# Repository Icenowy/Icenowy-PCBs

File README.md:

# Icenowy-PCBs
PCBs designed by Icenowy

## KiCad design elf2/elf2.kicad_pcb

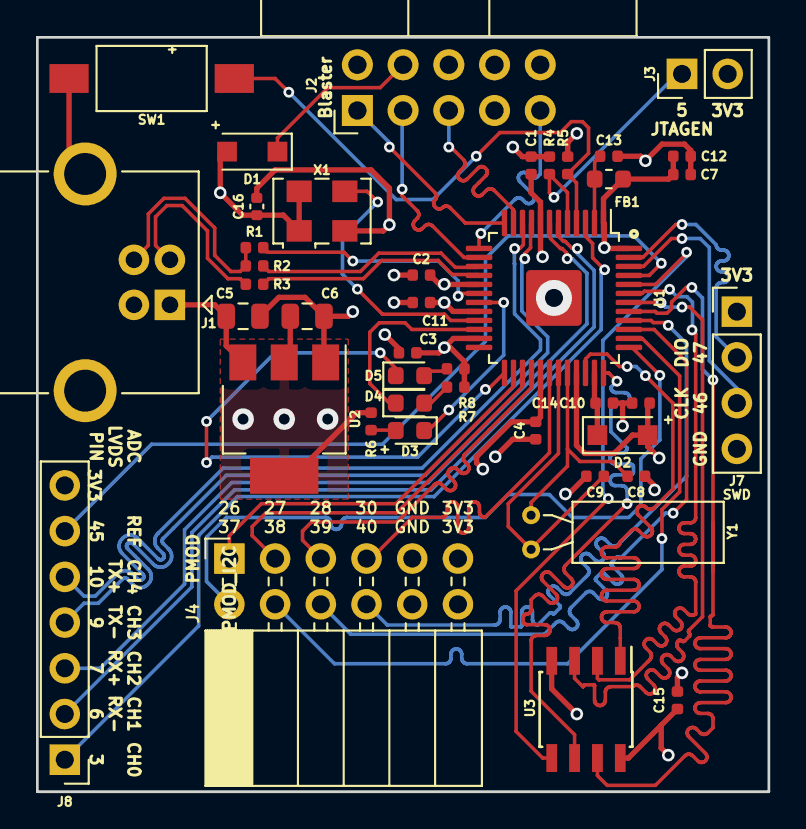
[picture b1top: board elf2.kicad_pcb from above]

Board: 4 copper layers, 40.6 x 41.9 mm, 42 parts (0 on the bottom side), 48 nets.

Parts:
C1, C2, C3, C4, C7, C10, C11, C12, C13, C14, C15, C16: 0.1uF; C_0402_1005Metric
C5, C6: 10uF; C_0805_2012Metric
C8, C9: 12pF; C_0402_1005Metric
D1, D2: 1N5819; D_SOD-123F
D3: RED; LED_0603_1608Metric
D4: GREEN; LED_0603_1608Metric
D5: BLUE; LED_0603_1608Metric
FB1: 300R; L_0603_1608Metric
J1: USB_B; USB_B_OST_USB-B1HSxx_Horizontal
J2: USB_Blaster; IDC-Header_2x05_P2.54mm_Horizontal
J3: JTAGEN; PinHeader_1x02_P2.54mm_Vertical
J4: PMOD; PinSocket_2x06_P2.54mm_Horizontal
J7: SWD; PinHeader_1x04_P2.54mm_Vertical
J8: ADC_LVDS; PinHeader_1x07_P2.54mm_Vertical
R1, R6, R7, R8: 1.5kR; R_0402_1005Metric
R2, R3: 47R; R_0402_1005Metric
R4, R5: 10kR; R_0402_1005Metric
SW1: RESET; SW_SPST_FSMSM
U1: EF2M45LG48; LQFP-48-1EP_7x7mm_P0.5mm_EP3.1x3.1mm
U2: AP1117-33; SOT-223-3_TabPin2
U3: AT25SF081-SSHD-X; SOIC-8_3.9x4.9mm_P1.27mm
X1: 24MHz; Oscillator_SMD_EuroQuartz_XO53-4Pin_5.0x3.2mm
Y1: 32768; Crystal_C38-LF_D3.0mm_L8.0mm_Horizontal

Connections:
+3V3: C1.2, C2.2, C3.2, C4.2, C6.1, C7.2, C10.1, C11.1, C12.1, C15.2, C16.1, D1.2, D2.2, FB1.1, J3.2, J4.11, J4.12, J7.1, J8.7, R5.1, R6.1, R7.1, R8.1, U1.1, U1.8, U1.17, U1.20, U1.23, U1.29, U1.33, U1.48, U2.2, U3.8, X1.1, X1.4
+5V: C5.1, J1.1, U2.3
+BATT: C14.2, D2.1, U1.35
/ADC_0: J8.1, U1.3
/ADC_REF: J8.6, U1.45
/CLK: U1.21, X1.3
/JTAGEN: J3.1, R4.1, U1.5
/LED_B: D5.1, U1.25
/LED_G: D4.1, U1.22
/LED_R: D3.1, U1.19
/LVDSRX_N: J8.2, U1.6
/LVDSRX_P: J8.3, U1.7
/LVDSTX_N: J8.4, U1.9
/LVDSTX_P: J8.5, U1.10
/PMOD_6P2_1: J4.2, U1.37
/PMOD_6P2_2: J4.4, U1.38
/PMOD_6P2_3: J4.6, U1.39
/PMOD_6P2_4: J4.8, U1.40
/PMOD_6P_1: J4.1, U1.26
/PMOD_6P_2: J4.3, U1.27
/PMOD_6P_3: J4.5, U1.28
/PMOD_6P_4: J4.7, U1.30
/PORT_D+: J1.3, R1.2, R2.2
/PORT_D-: J1.2, R3.2
/PROGRAMN: R5.2, SW1.1, U1.4
/QSPI_CS: U1.34, U3.1
/QSPI_IO0: U1.44, U3.5
/QSPI_IO1: U1.43, U3.2
/QSPI_IO2: U1.42, U3.3
/QSPI_IO3: U1.41, U3.7
/QSPI_SCK: U1.36, U3.6
/SWCLK: J7.3, U1.46
/SWDIO: J7.2, U1.47
/TCK: J2.1, U1.12
/TDI: J2.9, U1.13
/TDO: J2.3, U1.14
/TMS: J2.5, U1.11
/UD+: R2.1, U1.15
/UD-: R3.1, U1.16
/UPU: R1.1, U1.18
GND: C1.1, C2.1, C3.1, C4.1, C5.2, C6.2, C7.1, C8.2, C9.2, C10.2, C11.2, C12.2, C13.1, C14.1, C15.1, C16.2, J1.4, J1.5, J2.2, J2.10, J4.9, J4.10, J7.4, R4.2, SW1.2, U1.49, U2.1, U3.4, X1.2
unnamed: C8.1, U1.32, Y1.2
unnamed: C9.1, U1.31, Y1.1
unnamed: C13.2, FB1.2, U1.2
unnamed: D1.1, J2.4
unnamed: D3.2, R6.2
unnamed: D4.2, R7.2
unnamed: D5.2, R8.2

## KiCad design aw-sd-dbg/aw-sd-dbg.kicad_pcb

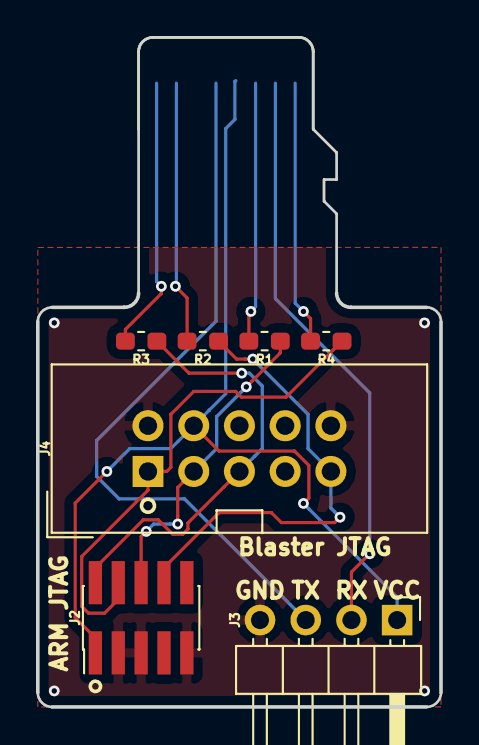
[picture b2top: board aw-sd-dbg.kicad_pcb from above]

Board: 2 copper layers, 22.4 x 37.2 mm, 8 parts (0 on the bottom side), 12 nets.

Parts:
J1: MicroSD
J2: ARM JTAG; PinHeader_2x05_P1.27mm_Vertical_SMD
J3: Conn_01x04_Male; PinHeader_1x04_P2.54mm_Horizontal
J4: Blaster JTAG; IDC-Header_2x05_P2.54mm_Vertical
R1, R2, R3, R4: 47R; R_0603_1608Metric_Pad1.05x0.95mm_HandSolder

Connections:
/CLK: J1.5, J3.3
/CMD: J1.3, R1.2
/DAT0: J1.7, R2.2
/DAT1: J1.8, R3.2
/DAT2: J1.1, R4.2
/DAT3: J1.2, J3.2
/JTCK_O: J2.4, J4.1, R4.1
/JTDI_O: J2.8, J4.9, R2.1
/JTDO_O: J2.6, J4.3, R1.1
/JTMS_O: J2.2, J4.5, R3.1
/VTGT: J1.4, J2.1, J3.1, J4.4
GND: J1.6, J2.3, J2.5, J2.9, J3.4, J4.2, J4.10

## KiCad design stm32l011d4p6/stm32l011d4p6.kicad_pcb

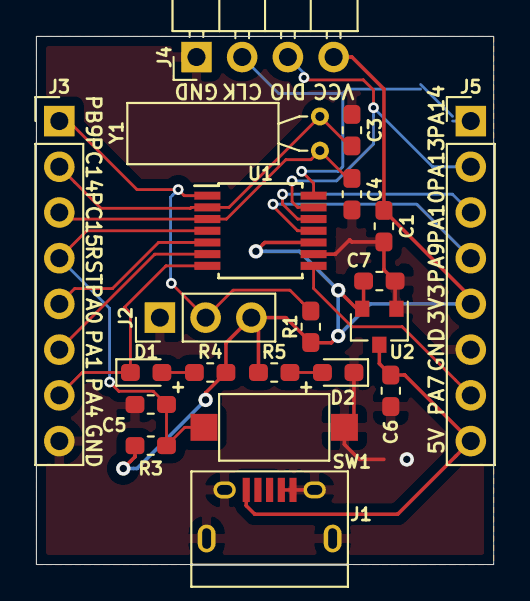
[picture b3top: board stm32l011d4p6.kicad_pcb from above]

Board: 2 copper layers, 25.4 x 29.3 mm, 21 parts (0 on the bottom side), 17 nets.

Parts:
C1, C5, C6, C7: 0.1uF; C_0603_1608Metric_Pad1.05x0.95mm_HandSolder
C3, C4: 12pF; C_0603_1608Metric_Pad1.05x0.95mm_HandSolder
D1: GREEN; LED_0603_1608Metric_Pad1.05x0.95mm_HandSolder
D2: RED; LED_0603_1608Metric_Pad1.05x0.95mm_HandSolder
J1: USB_B_Micro; USB_Micro-B_Connector
J2: BOOT0; PinHeader_1x03_P2.54mm_Vertical
J3: LEFT; PinHeader_1x08_P2.54mm_Vertical
J4: SWD; PinHeader_1x04_P2.54mm_Horizontal
J5: RIGHT; PinHeader_1x08_P2.54mm_Vertical
R1, R3: 10kR; R_0603_1608Metric_Pad1.05x0.95mm_HandSolder
R4, R5: 1.5kR; R_0603_1608Metric_Pad1.05x0.95mm_HandSolder
SW1: SW_Push; SW_SPST_CK_RS282G05A3
U1: STM32L011D4Px; TSSOP-14_4.4x5mm_P0.65mm
U2: SC662K-3.3V; SOT-23
Y1: 32768Hz; Crystal_C38-LF_D3.0mm_L8.0mm_Horizontal

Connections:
/BOOT0: J2.2, J3.1, R1.1, U1.1
/NRST: C5.1, J3.4, R3.2, SW1.1, U1.4
/OSC_IN: C3.2, J3.2, U1.2, Y1.1
/OSC_OUT: C4.2, J3.3, U1.3, Y1.2
/PA0: J3.5, U1.5
/PA1: J3.6, U1.6
/PA4: D1.1, J3.7, U1.7
/PA7: J5.7, U1.8
/PA9: J5.4, U1.11
/PA10: J5.3, U1.12
/PA13: J4.3, J5.2, U1.13
/PA14: J4.2, J5.1, U1.14
GND: C1.1, C3.1, C4.1, C5.2, C6.1, C7.2, D2.1, J1.4, J1.5, J1.6, J2.1, J3.8, J4.1, J5.6, SW1.2, U1.9, U2.1
unnamed: D1.2, R4.2
unnamed: D2.2, R5.2
VBUS: C6.2, J1.1, J5.8, U2.3
VCC: C1.2, C7.1, J2.3, J4.4, J5.5, R1.2, R3.1, R4.1, R5.1, U1.10, U2.2

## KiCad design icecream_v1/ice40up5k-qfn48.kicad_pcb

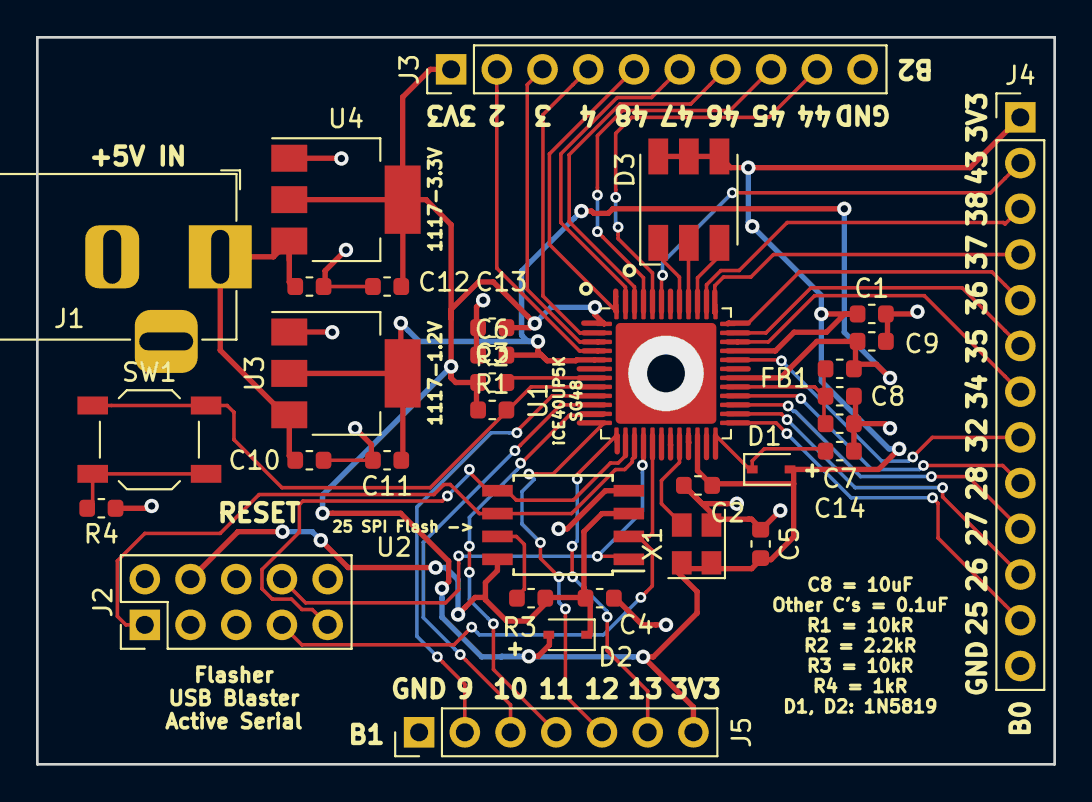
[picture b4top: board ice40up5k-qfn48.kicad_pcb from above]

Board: 2 copper layers, 56.5 x 40.4 mm, 33 parts (0 on the bottom side), 43 nets.

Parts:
C1, C2, C3, C4, C5, C6, C7, C9, C10, C11, C12, C13, C14: 0.1uF; C_0603_1608Metric
C8: 10uF; C_0603_1608Metric
D1, D2: 1N5819; D_SOD-323
D3: LED_RGB; LED_RGB_5050-6
FB1: Ferrite_Bead; L_0603_1608Metric
J1: 5V 3.5mm/1.35mm; BarrelJack_Horizontal
J2: Flasher; PinHeader_2x05_P2.54mm_Vertical
J3: Bank 2; PinHeader_1x10_P2.54mm_Vertical
J4: Bank 0; PinHeader_1x13_P2.54mm_Vertical
J5: Bank 1; PinHeader_1x07_P2.54mm_Vertical
R1, R3: 10kR; R_0603_1608Metric
R2: 2.2kR; R_0603_1608Metric
R4: 1kR; R_0603_1608Metric
SW1: Button; SW_SPST_TL3342
U1: ICE40UP5K-SG48ITR; QFN-48-1EP_7x7mm_P0.5mm_EP5.6x5.6mm
U2: W25Q80; SOIJ-8_5.3x5.3mm_P1.27mm
U3: LD1117S12TR_SOT223; SOT-223-3_TabPin2
U4: LD1117S33TR_SOT223; SOT-223-3_TabPin2
X1: 50MHz; Oscillator_SMD_Abracon_ASE-4Pin_3.2x2.5mm

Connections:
+1V2: C6.2, C9.2, C11.1, FB1.1, U1.5, U1.30, U3.2
+3.3VP: C4.1, D2.1, J2.4, R3.1, U2.3, U2.8
+3V3: C1.1, C2.1, C3.1, C5.1, C13.1, D1.2, D2.2, D3.4, D3.5, D3.6, J3.1, J4.1, J5.7, R1.1, R2.1, U1.1, U1.22, U1.33, U4.2, X1.1, X1.4
+5V: C10.1, C12.1, J1.1, U3.3, U4.3
/2: J3.4, U1.2
/3: J3.3, U1.3
/4: J3.2, U1.4
/9: J5.2, U1.9
/10: J5.3, U1.10
/11: J5.4, U1.11
/12: J5.5, U1.12
/13: J5.6, U1.13
/25: J4.12, U1.25
/26: J4.11, U1.26
/27: J4.10, U1.27
/28: J4.9, U1.28
/32: J4.8, U1.32
/34: J4.7, U1.34
/35: J4.6, U1.35
/36: J4.5, U1.36
/37: J4.4, U1.37
/38: J4.3, U1.38
/43: J4.2, U1.43
/44: J3.9, U1.44
/45: J3.8, U1.45
/46: J3.7, U1.46
/47: J3.6, U1.47
/48: J3.5, U1.48
/CDONE: R2.2, U1.7
/CLK_50M: U1.20, X1.3
/CRESET: R1.2, SW1.1, U1.8
/ICE_SCK: J2.1, U1.15, U2.6
/ICE_SI: J2.7, U1.17, U2.2
/ICE_SO: J2.9, U1.14, U2.5
/ICE_SS: J2.8, U1.16, U2.1
GND: C1.2, C2.2, C3.2, C4.2, C5.2, C6.1, C7.1, C8.1, C9.1, C10.2, C11.2, C12.2, C13.2, C14.2, J1.2, J2.2, J2.10, J3.10, J4.13, J5.1, R4.1, U1.49, U2.4, U3.1, U4.1, X1.2
unnamed: C7.2, C8.2, FB1.2, U1.29
unnamed: C14.1, D1.1, U1.24
unnamed: D3.1, U1.41
unnamed: D3.2, U1.40
unnamed: D3.3, U1.39
unnamed: R3.2, U2.7
unnamed: R4.2, SW1.2

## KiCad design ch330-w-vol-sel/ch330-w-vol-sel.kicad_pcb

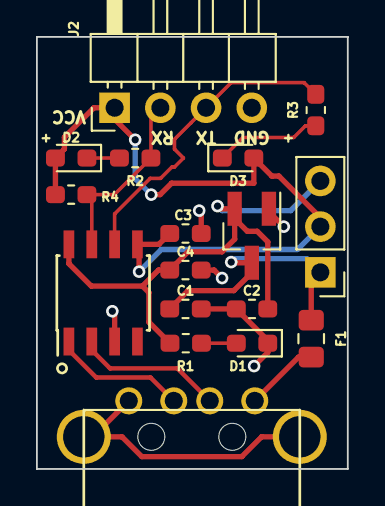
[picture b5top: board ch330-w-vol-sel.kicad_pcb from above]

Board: 2 copper layers, 17.3 x 24.0 mm, 17 parts (0 on the bottom side), 12 nets.

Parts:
C1, C2: 1uF; C_0603_1608Metric_Pad1.05x0.95mm_HandSolder
C3, C4: 0.1uF; C_0603_1608Metric_Pad1.05x0.95mm_HandSolder
D1: RED; LED_0603_1608Metric_Pad1.05x0.95mm_HandSolder
D2, D3: YELLOW; LED_0603_1608Metric_Pad1.05x0.95mm_HandSolder
F1: >5.2V 100mA; R_0805_2012Metric_Pad1.15x1.40mm_HandSolder
J1: USB_A; USB_A_Plug
J2: UART; PinHeader_1x04_P2.54mm_Horizontal
J3: VOL SEL; PinHeader_1x03_P2.54mm_Vertical
R1, R2, R3: 1.5kR; R_0603_1608Metric_Pad1.05x0.95mm_HandSolder
R4: 4.7kR; R_0603_1608Metric_Pad1.05x0.95mm_HandSolder
U1: CH330N; SOIC-8_3.9x4.9mm_P1.27mm
U2: XC6206P33; SOT-23_Handsoldering

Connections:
+3V3: C2.1, C4.2, J3.3, R1.2, U1.8, U2.2
/D+: J1.3, U1.1
/D-: J1.2, U1.2
/RX: J2.2, R2.1, R4.2, U1.7
/TX: J2.3, R3.2, U1.6
GND: C1.2, C2.2, C3.2, C4.1, D1.1, J1.4, J1.5, J2.4, U1.3, U2.1
unnamed: D1.2, R1.1
unnamed: D2.1, R2.2
unnamed: D3.1, R3.1
unnamed: F1.2, J1.1
VBUS: C1.1, F1.1, J3.1, U2.3
VCC: C3.1, D2.2, D3.2, J2.1, J3.2, R4.1, U1.5

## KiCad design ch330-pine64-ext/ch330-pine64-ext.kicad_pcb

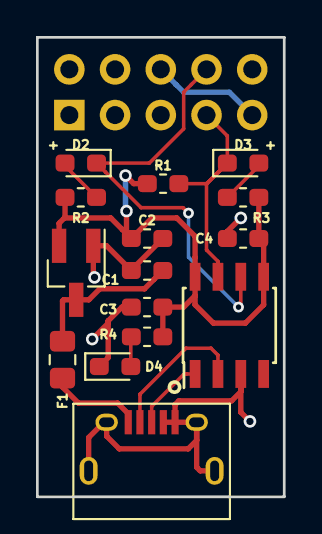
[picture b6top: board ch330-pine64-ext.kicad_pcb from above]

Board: 2 copper layers, 13.7 x 25.5 mm, 16 parts (1 on the bottom side), 11 nets.

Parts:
C1, C2: 1uF; C_0603_1608Metric_Pad1.05x0.95mm_HandSolder
C3, C4: 0.1uF; C_0603_1608Metric_Pad1.05x0.95mm_HandSolder
D2, D3: Yellow; LED_0603_1608Metric_Pad1.05x0.95mm_HandSolder
D4: Red; LED_0603_1608Metric_Pad1.05x0.95mm_HandSolder
F1: 1R, 5W; R_0805_2012Metric_Pad1.15x1.40mm_HandSolder
J1: USB_B_Micro; USB_Micro-B_Connector
J2: Pine64_EXP; PinSocket_2x05_P2.54mm_Vertical
R1: 10kR; R_0603_1608Metric_Pad1.05x0.95mm_HandSolder
R2, R3, R4: 1.5kR; R_0603_1608Metric_Pad1.05x0.95mm_HandSolder
U1: CH330N; SOIC-8_3.9x4.9mm_P1.27mm
U2: XC6206P33; SOT-23_Handsoldering

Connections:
+3V3: C2.1, C3.1, C4.1, R1.1, R2.1, R3.1, R4.2, U1.5, U1.8, U2.2
/D+: J1.3, U1.1
/D-: J1.2, U1.2
GND: C1.1, C2.2, C3.2, C4.2, D4.1, J1.4, J1.5, J1.6, J2.6, J2.9, U1.3, U2.1
unnamed: D2.1, J2.8, U1.6
unnamed: D2.2, R2.2
unnamed: D3.1, J2.7, R1.2, U1.7
unnamed: D3.2, R3.2
unnamed: D4.2, R4.1
unnamed: F1.2, J1.1
VBUS: C1.2, F1.1, U2.3

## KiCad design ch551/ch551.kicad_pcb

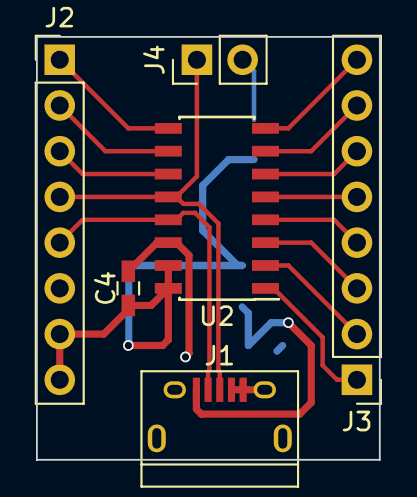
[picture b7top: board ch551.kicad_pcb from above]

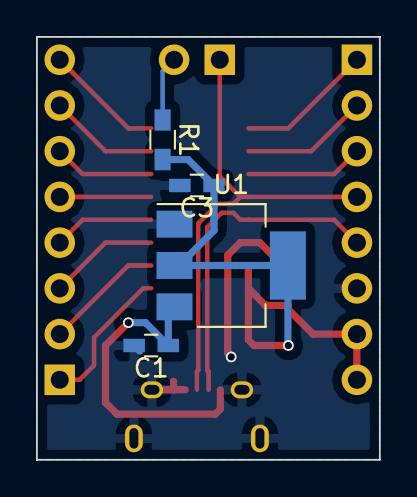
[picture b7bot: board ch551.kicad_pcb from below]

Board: 2 copper layers, 19.0 x 23.5 mm, 10 parts (4 on the bottom side), 17 nets.

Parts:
C1, C3: 10μF; C_0603_HandSoldering
C4: 0.1μF; C_0603_HandSoldering
J1: USB_OTG; USB_Micro-B
J2, J3: Conn_01x08; Pin_Header_Straight_1x08_Pitch2.54mm
J4: Conn_01x02; Pin_Header_Straight_1x02_Pitch2.54mm
R1: 10K; R_0603_HandSoldering
U1: LM1117-3.3; SOT-223
U2: CH551G; SOIC-16_3.9x9.9mm_Pitch1.27mm

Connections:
+3V3: C3.1, C4.1, J2.7, J2.8, R1.2, U1.2, U1.4, U2.15, U2.16
/D+: J1.3, J2.4, J4.1, U2.12
/D-: J1.2, J2.5, U2.13
GND: C1.2, C3.2, C4.2, J1.4, J1.5, J1.6, J2.6, U1.1, U2.14
unnamed: J2.1, U2.9
unnamed: J2.2, U2.10
unnamed: J2.3, U2.11
unnamed: J3.1, U2.1
unnamed: J3.2, U2.2
unnamed: J3.3, U2.3
unnamed: J3.4, U2.4
unnamed: J3.5, U2.5
unnamed: J3.6, U2.6
unnamed: J3.7, U2.7
unnamed: J3.8, U2.8
unnamed: J4.2, R1.1
VBUS: C1.1, J1.1, U1.3

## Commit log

2018-07-30 first batch
2018-07-30 usb-data-blackhole
2018-08-30 update new ch330 designs
2018-09-01 ch330-w-vol-sel: fixes
2018-09-02 ch330-w-vol-sel: misc silkscreen fix
2019-02-23 add libs from adafruit
2019-03-01 icecream_v1: push, tested
2019-04-05 elf2: add v1
2019-06-22 stm32_fxp6: push, tested but added silkprint fix
    The original design tested didn't have SWD silkprint. I added it and pushed.
2020-04-10 fix USB_A_Plug position holes and fix usb-data-blackhole
2020-07-28 add my new packages
2020-07-28 stm32l011d4p6: add as a simple STM32 board
2020-07-28 add lib from 3340
2020-07-28 gitignore: ignore fp-info-cache
2020-11-17 ch330-pine64-ext: migrate
2021-06-20 aw-sd-dbg: add
2021-12-16 update elf2 to v2
